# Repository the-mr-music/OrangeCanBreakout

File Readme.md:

# Orange PI CAN Breakout

T. Music - 01/2020

## Project Status

```
PCB Design Complete - Next up is assembly and testing
```

## Introduction

Some time ago I had ordered myself a Raspberry Pi Zero with the intention to use it as a wireless debugger. The performance of it and the system in general however did not live up to my expected standards, so I had decided to give another single board computer a shot. The requirements whilst picking were easy integreatibility (USB on pinheaders), sufficiently high computational power (something the rpi zero somewhat lacked) and naturally - WiFi. In the end the Orange Pi Zero Plus 2 (Allwinner H5 core) won and was ordered.

On top of that I thought about extending the capability of said system through optional modules, which can be addressed through a python api running on the orange pi. One criteria was to provide somewhat sufficient data rate for hobbyist use cases and to keep the hardware overhead low. After reading through a few bus systems and protocols I reached the decision to use CAN bus. Cheap controllers by ST have already CAN controllers built in and require only a transceiver in the range of a few cents. These STM32 support data rates up to 1 Mbit/s, enough for small amounts of measurement data as well as control messages.
If one needs higher data rates, the CAN FD standard increases the message's data bitrate to up to 8 Mbit/s. Whilst CAN FD is backwards compatible to regular CAN, upwards compatibility is not given, therefore legacy and FD nodes should not be mixed on one bus.

## Description
< write me >

## Design Notes

Only wanted one distributor. Due to my previous positive experiences, I again went for LCSC.  
With the design finalised, the PCB was sent off to JLCPCB.

## Schematic
Click here to open the [Schematic Revision 1](Production_Data_Rev_1/can_breakout_pcb_rev1.pdf).

## Renders

### Front

### Back

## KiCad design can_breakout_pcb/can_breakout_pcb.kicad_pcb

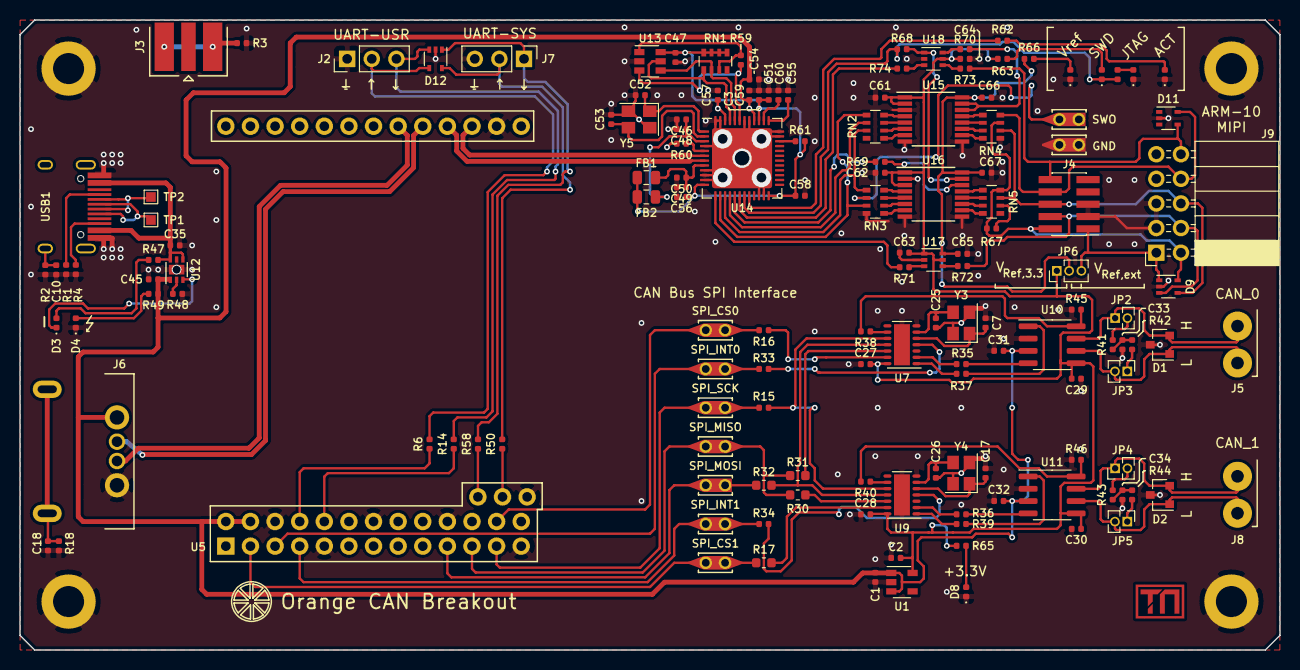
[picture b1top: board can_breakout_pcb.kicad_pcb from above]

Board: 2 copper layers, 130.0 x 65.0 mm, 154 parts (0 on the bottom side), 127 nets.

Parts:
C1, C2, C35, C45, C48, C50, C51, C54: 4.7uF; C_0402_1005Metric
C3, C10, C18, C29, C30, C31, C32, C46, C47, C49, C55, C56, C57, C58, C59, C60, C61, C62, C63, C64, C65, C66, C67: 100nF; C_0402_1005Metric
C7, C17, C25, C26: 30pF; C_0402_1005Metric
C27, C28: 1uF; C_0402_1005Metric
C33, C34: 4.7nF; C_0402_1005Metric
C52, C53: 12pF; C_0402_1005Metric
D1, D2: NUP2105L; SOT-23
D3: Red; LED_0402_1005Metric
D4: Green; LED_0402_1005Metric
D5: White; LED_0402_1005Metric
D6: SWD_LED; LED_0402_1005Metric
D7: JTAG_LED; LED_0402_1005Metric
D8: Orange; LED_0402_1005Metric
D9, D11, D12: PESD3V3L4UG; SOT-353_SC-70-5
D10: Vref_LED; LED_0402_1005Metric
FB1, FB2: 2A 0.1DCR; L_0805_2012Metric
H1, H2, H3, H4: MountingHole_Pad; MountingHole_3.2mm_M3_DIN965_Pad
J2, J7: Conn_01x03_Male; PinHeader_1x03_P2.54mm_Vertical
J3: Conn_Coaxial; SMA_6x6mm_MidMount
J4: Conn_ARM_JTAG_SWD_10; PinHeader_2x05_P1.27mm_Vertical_SMD
J5, J8: DB125-3.81-2P
J6: USB_A; USB_AF_DIP
J9: Conn_ARM_JTAG_SWD_10; PinSocket_2x05_P2.54mm_Horizontal
JP2, JP3, JP4, JP5: Jumper; PinHeader_1x02_P1.27mm_Vertical
JP6: Jumper_3_Open; PinHeader_1x03_P1.27mm_Vertical
LOGO1: Logo_TM_small; TM_logo
R1, R4: 5.1k; R_0402_1005Metric
R2, R18: 100k; R_0402_1005Metric
R3: opt - 0R; R_0402_1005Metric
R6, R14, R15, R16, R33, R34, R50, R58, R68, R69, R70, R71, R72, R73, R74: 22R; R_0402_1005Metric
R17, R30, R31, R32: 22R; R_0603_1608Metric
R35, R36, R37, R38, R39, R40, R67: 0R; R_0402_1005Metric
R41, R42, R43, R44: 60R; R_0402_1005Metric
R45, R46: DNP; R_0402_1005Metric
R47, R49: Rled; R_0402_1005Metric
R48: 15k; R_0402_1005Metric
R59: 2k; R_0402_1005Metric
R60: 12k; R_0402_1005Metric
R61: 10k; R_0402_1005Metric
R62, R63, R64, R65, R66: R_LED; R_0402_1005Metric
RN1: 10k; R_Array_Convex_4x0603
RN2, RN3, RN4, RN5: 22R; R_Array_Convex_4x0603
TP1, TP2: TestPoint; TestPoint_Pad_1.0x1.0mm
TP3: SPI_MOSI; TestPadClip_0.25
TP5: SPI_MISO; TestPadClip_0.25_Passthrough
TP6: SPI_SCK; TestPadClip_0.25_Passthrough
TP7: SPI_CS1; TestPadClip_0.25_Passthrough
TP8: SPI_CS0; TestPadClip_0.25_Passthrough
TP9: SPI_INT0; TestPadClip_0.25_Passthrough
TP10: SPI_INT1; TestPadClip_0.25_Passthrough
TP11: GND; TestPadClip_0.25
TP12: SWO; TestPadClip_0.25
U1: TLV73333PDBV; SOT-23-5
U5: OrangePiZero2Plus; OPi_Zero_plus_2_NoMountHoles
U7, U9: MCP2517FD-xJHA; DFN-14-1EP_3x4.5mm_P0.65mm_EP1.65x4.25mm
U10, U11: MCP2542FDxMF; SOIC-8_3.9x4.9mm_P1.27mm
U12: AP2553; DFN-6-1EP_2x2mm_P0.65mm_EP1x1.6mm
U13: 93LC56BT-I/OT; SOT-23-6
U14: FT232H; QFN-48-1EP_8x8mm_P0.5mm_EP6.2x6.2mm
U15, U16: SN74AVC4T245PW; TSSOP-16_4.4x5mm_P0.65mm
U17: SN74AVC1T45DCK; SOT-363_SC-70-6
U18: 74LVC2G06; SOT-363_SC-70-6
USB1: HRO-TYPE-C-31-M-12; HRO-TYPE-C-31-M-12-HandSoldering
Y3, Y4: SMD-3225_4P20MHZ20PF10PPM; Crystal_SMD_3225-4Pin_3.2x2.5mm
Y5: ABM8G-12.000MHZ-B4Y-T; Crystal_SMD_Abracon_ABM8G-4Pin_3.2x2.5mm

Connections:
+3V3: C2.1, C27.2, C28.2, C29.2, C30.2, C61.1, C62.1, C63.1, C64.1, JP6.1, R63.1, R65.1, U1.5, U7.14, U9.14, U10.5, U11.5, U15.1, U15.2, U16.1, U16.3, U17.1, U17.5, U18.5
+5V: C1.1, C31.2, C32.2, C45.1, C54.1, C59.1, J6.1, R49.1, U1.1, U1.3, U5.2, U5.4, U10.3, U11.3, U12.1, U14.40
+VSW: C65.1, C66.1, C67.1, JP6.2, R66.1, U15.16, U16.16, U17.6
/can.sch/SPI_CLK: R15.1, TP6.1, U5.23
/can.sch/SPI_CS0: R16.2, TP8.1, U5.24
/can.sch/SPI_CS1: R17.2, TP7.1, U5.3
/can.sch/SPI_INT0: R33.2, TP9.1, U5.5
/can.sch/SPI_INT1: R34.2, TP10.1, U5.7
/can.sch/SPI_MISO: R30.2, R31.2, TP5.1, U5.21
/can.sch/SPI_MOSI: R32.2, TP3.1, U5.19
/ftdi/DBG_RST: D11.4, J4.10, J9.10, R73.1
/ftdi/DBG_TCK: D9.3, J4.4, J9.4, R72.1
/ftdi/DBG_TDI: D11.5, J4.8, J9.8, RN4.8
/ftdi/DBG_TDO: D9.4, J4.6, J9.6, RN4.6, RN5.7
/ftdi/DBG_TMS: D9.5, J4.2, J9.2, R67.1, RN4.7, RN5.8
/ftdi/DBG_VREF: D9.1, J4.1, J9.1, JP6.3
/ftdi/FTDI_3V3: C3.1, C47.2, C51.1, C56.1, C57.1, C58.1, FB1.1, FB2.1, R61.2, RN1.5, RN1.6, RN1.7, RN1.8, U13.6, U14.12, U14.24, U14.39, U14.46
/ftdi/FTDI_USB_DN: U5.E3, U14.6
/ftdi/FTDI_USB_DP: U5.E4, U14.7
/ftdi/FT_LED: R62.1, U14.20
/ftdi/FT_RST: R74.2, U14.18
/ftdi/FT_SWD_EN: D6.1, R64.1, R68.2, U14.19
/ftdi/FT_SWD_OE: R69.2, U14.17
/ftdi/SWD_EN: R68.1, U16.15, U18.1
/ftdi/SWD_OE: R69.1, U16.14
/ftdi/~SWD_EN~: R70.1, U15.14, U15.15
/orangepi/USB3_DN: J6.2, U5.E5
/orangepi/USB3_DP: J6.3, U5.E6
/orangepi/USB_DN: TP2.1, USB1.5, USB1.7
/orangepi/USB_DP: TP1.1, USB1.6, USB1.8
GND: C1.2, C2.2, C3.2, C7.1, C10.1, C17.1, C18.1, C25.2, C26.2, C27.1, C28.1, C29.1, C30.1, C31.1, C32.1, C33.1, C34.1, C35.2, C45.2, C46.2, C47.1, C48.2, C49.2, C50.2, C51.2, C52.2, C53.2, C54.2, C55.1, C56.2, C57.2, C58.2, C59.2, C60.2, C61.2, C62.2, C63.2, C64.2, C65.2, C66.2, C67.2, D1.3, D2.3, D4.1, D5.1, D7.1, D8.1, D9.2, D10.1, D11.2, D12.2, H1.1, H2.1, H3.1, H4.1, J2.1, J4.3, J4.5, J6.4, J7.3, J9.3, J9.5, R1.2, R2.2, R3.2, R4.2, R18.2, R45.2, R46.2, R48.2, R60.2, RN3.4, RN4.5, TP11.1, U1.2, U5.6, U5.9, U5.14, U5.20, U5.25, U5.E2, U5.U1, U7.7, U7.15, U9.7, U9.15, U10.2, U11.2, U12.5, U12.7, U13.2, U14.4, U14.9, U14.10, U14.11, U14.22, U14.23, U14.35, U14.36, U14.41, U14.42, U14.47, U14.48, U14.49, U15.3, U15.8, U15.9, U16.2, U16.8, U16.9, U17.2, U18.2, USB1.1, USB1.12, Y3.2, Y3.4, Y4.2, Y4.4, Y5.2, Y5.4
unnamed: C7.2, U7.5, Y3.1
unnamed: C10.2, R2.1, USB1.13
unnamed: C17.2, U9.5, Y4.1
unnamed: C18.2, J6.5, R18.1
unnamed: C25.1, U7.6, Y3.3
unnamed: C26.1, U9.6, Y4.3
unnamed: C33.2, R41.2, R42.1
unnamed: C34.2, R43.2, R44.1
unnamed: C46.1, C48.1, FB2.2, U14.3
unnamed: C49.1, C50.1, FB1.2, U14.8
unnamed: C52.1, U14.1, Y5.1
unnamed: C53.1, U14.2, Y5.3
unnamed: C55.2, U14.37
unnamed: C60.1, U14.38
unnamed: D1.1, J5.1, JP3.2, U10.6
unnamed: D1.2, J5.2, JP2.1, U10.7
unnamed: D2.1, J8.1, JP5.2, U11.6
unnamed: D2.2, J8.2, JP4.1, U11.7
unnamed: D3.1, U12.3
unnamed: D3.2, R47.2
unnamed: D4.2, R49.2
unnamed: D5.2, R62.2
unnamed: D6.2, R63.2
unnamed: D7.2, R64.2
unnamed: D8.2, R65.2
unnamed: D10.2, R66.2
unnamed: D12.1, J7.1, R58.2
unnamed: D12.3, J2.3, R14.2
unnamed: D12.4, J2.2, R6.2
unnamed: D12.5, J7.2, R50.2
unnamed: J3.2, R3.1
unnamed: JP2.2, R41.1
unnamed: JP3.1, R42.2
unnamed: JP4.2, R43.1
unnamed: JP5.1, R44.2
unnamed: R1.1, USB1.4
unnamed: R4.1, USB1.10
unnamed: R6.1, U5.8
unnamed: R14.1, U5.10
unnamed: R15.2, U7.10, U9.10
unnamed: R16.1, U7.13
unnamed: R17.1, U9.13
unnamed: R30.1, U9.12
unnamed: R31.1, U7.12
unnamed: R32.1, U7.11, U9.11
unnamed: R33.1, U7.4
unnamed: R34.1, U9.4
unnamed: R35.1, U7.2
unnamed: R35.2, U10.4
unnamed: R36.1, U9.2
unnamed: R36.2, U11.4
unnamed: R37.1, U7.1
unnamed: R37.2, U10.1
unnamed: R38.1, U7.9
unnamed: R38.2, R45.1, U10.8
unnamed: R39.1, U9.1
unnamed: R39.2, U11.1
unnamed: R40.1, U9.9
unnamed: R40.2, R46.1, U11.8
unnamed: R48.1, U12.2
unnamed: R50.1, U5.U2
unnamed: R58.1, U5.U3
unnamed: R59.1, U13.3, U14.43
unnamed: R59.2, RN1.3, U13.1
unnamed: R60.1, U14.5
unnamed: R61.1, U14.34
unnamed: R67.2, RN5.6
unnamed: R70.2, U18.6
unnamed: R71.1, U17.3
unnamed: R71.2, U14.13
unnamed: R72.2, U17.4
unnamed: R73.2, U18.4
unnamed: R74.1, U18.3
unnamed: RN1.1, U13.5, U14.45
unnamed: RN1.2, U13.4, U14.44
unnamed: RN2.1, RN3.3, U14.14
unnamed: RN2.2, U14.16
unnamed: RN2.3, RN3.1, U14.15
unnamed: RN2.5, U15.7
unnamed: RN2.6, U15.6
unnamed: RN2.7, U15.5
unnamed: RN2.8, U15.4
unnamed: RN3.2, TP12.1
unnamed: RN3.5, U16.7
unnamed: RN3.6, U16.6
unnamed: RN3.7, U16.5
unnamed: RN3.8, U16.4
unnamed: RN4.1, U15.13
unnamed: RN4.2, U15.12
unnamed: RN4.3, U15.11
unnamed: RN4.4, U15.10
unnamed: RN5.1, U16.13
unnamed: RN5.2, U16.12
unnamed: RN5.3, U16.11
unnamed: RN5.4, U16.10
VBUS: C35.1, R47.1, U12.4, U12.6, USB1.2, USB1.11

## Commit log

2020-01-11 Added first version of readme, licensing and gitignore
2020-01-11 Added gerber files for revision 1
2020-01-11 Added PCB Rev. 1
2020-02-05 Working on readme

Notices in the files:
Readme.md:
License: CC BY-SA 4.0
can_breakout_pcb/can_breakout_pcb.kicad_pcb:
CC BY-SA 4.0
